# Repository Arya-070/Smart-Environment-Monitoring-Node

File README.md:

# 🌿 Smart Environment Monitoring Node  
📡 ESP32-WROOM-32 + LoRa + BME280 + OLED | USB Powered | Custom PCB

──────────────────────────────────────────────

## 📌 Overview

This project is a compact, power-efficient, and long-range **environment monitoring system** based on the **ESP32-WROOM-32 chip**. It measures temperature, humidity, and pressure using the **BME280 sensor**, displays real-time values on a **0.96” OLED display**, and transmits the data via **LoRa SX1262** for remote monitoring.  

All hardware is designed on a **custom 2-layer PCB** and powered via a **USB Micro-B port**, with built-in USB-to-Serial conversion and auto-upload support for seamless firmware flashing.

---

## ✨ Project Highlights

• 🔧 Fully custom-designed PCB (2-layer) using KiCad  
• 📡 Long-range LoRa communication using SX1262  
• 🌡 Environmental monitoring using BME280  
• 🖥 Local data display via 0.96” I2C OLED  
• 🔌 USB-powered with CH340C USB-to-Serial interface  
• ⏩ Auto-upload circuit using NPN transistors  
• 🔁 Reset + Boot buttons like ESP32 Dev board  
• 📍Test points for VCC & GND for easy debugging  
• 🔋 AMS1117-based 3.3V regulator (if needed)  

---

## 📌  ESP32 GPIO Pinout & Connections 

| GPIO Pin   | Connected To              | Function / Role                     |
|------------|---------------------------|--------------------------------------|
| GPIO 0     | Q2 (Transistor)           | BOOT (Auto Upload via DTR)          |
| GPIO 1 (TXD)| CH340C RXD               | UART Transmission                    |
| GPIO 3 (RXD)| CH340C TXD               | UART Reception                       |
| GPIO 4     | SX1262 NSS                | SPI Chip Select (LoRa)              |
| GPIO 5     | SX1262 BUSY               | LoRa Busy Status                    |
| GPIO 14    | SX1262 SCK                | SPI Clock                           |
| GPIO 18    | SX1262 MISO               | SPI MISO                            |
| GPIO 19    | SX1262 MOSI               | SPI MOSI                            |
| GPIO 21    | OLED SDA                  | I2C Data (Display)                  |
| GPIO 22    | OLED SCL                  | I2C Clock (Display)                 |
| GPIO EN    | Q1 (Transistor)           | EN (Auto Reset via RTS)             |
| GPIO 23    | SX1262 DIO1               | LoRa Interrupt                      |
| GPIO 16    | SX1262 DIO2               | LoRa General-Purpose I/O            |
| GPIO 17    | BME280 SCK                | SPI Clock (Sensor)                  |
| GPIO 2     | LED (Optional)            | Debug LED Output                    |
| GPIO 13    | SX1262 NSS (2nd)          | SPI Slave Select (Alt, Unused?)     |
| GPIO 12,15 | —                         | Reserved / Available for future use |

🔍 *See schematic for exact net labels and detailed mapping.*

---

## 🔍 Use Case Acknowledgement

This project is ideal for:

• Agricultural field condition monitoring  
• Weather stations (indoor or outdoor)  
• Smart home environmental logging  
• Educational IoT demonstrations  
• Smart city sensor node deployment  
• Remote sensing with LoRa infrastructure

---

## 🧭 System Architecture

---

## 🧩 Component Summary

| No. | Component              | Interface | Description                                  |
|-----|------------------------|-----------|----------------------------------------------|
| 1   | ESP32-WROOM-32         | -         | Main MCU (WiFi, BLE, Dual Core)              |
| 2   | BME280 (SPI)           | SPI       | Temp, Pressure, Humidity sensor              |
| 3   | OLED 0.96” Display     | I2C       | SSD1306, 128x64 pixel display                |
| 4   | SX1262IMLTRT (QFN)     | SPI       | LoRa transceiver (433/868/915MHz)            |
| 5   | AMS1117-3.3V Regulator | Power     | Converts 5V USB to 3.3V (optional)           |
| 6   | CH340C USB to Serial   | UART      | USB programming interface                    |
| 7   | 40MHz Crystal Oscillator| CLK      | ESP32 clock source                           |
| 8   | Push Buttons (2x)      | GPIO/EN   | Boot and Reset functionality                 |
| 9   | LED + Resistor         | Power     | Power-on indicator                           |
| 10  | Capacitors (0.1µF, 10µF)| Power    | Decoupling & filtering                       |
| 11  | Test Points (TP1/TP2)  | -         | For debugging (3.3V and GND)                 |
| 12  | Micro USB Port         | Power     | Power + Serial communication                 |
| 13  | Resistors (10k, 1k)    | Logic     | Pull-ups and transistor base resistors       |
| 14  | NPN Transistors (x2)   | Auto Upload | Connected to DTR/RTS                        |
| 15  | Conn_01x2 / 01x4 / 01x8| Header    | GPIO/I2C/Power breakout (optional)           |

---

## 💾 Firmware Summary

• Platform: Arduino Framework  
• Libraries:
  - `Adafruit_BME280` (SPI)
  - `U8g2lib` / `Adafruit_SSD1306`
  - `RadioLib` or `LoRa` for SX1262
• Logic:
  - Read sensor values → Display on OLED → Send via LoRa
• Auto-upload handled via CH340C + transistor toggling of IO0 and EN

---

## 🧪 Test Points

| Label | Connected To | Use                      |
|-------|--------------|---------------------------|
| TP1   | 3.3V         | Voltage test/debug        |
| TP2   | GND          | Ground continuity check   |

---

## 📦 Folder Structure

```
Smart-Environment-Monitoring-Node/
│
├── SCHEMATIC/
│   ├── Smart_Env_monitoring_Node.kicad_sch
│   ├── Smart_Env_monitoring_Node.pdf
│  
├── Backup_ZIP
│
├── PCB/
│   ├──  Smart_Env_monitoring_Node.kicad_pcb
│   ├──  Smart_Env_monitoring_Node.kicad_pro
│   ├──  Smart_Env_monitoring_Node.csv
│   ├── Gerber_Files/
│   ├── F_Cu.gbr
│   ├── B_Cu.gbr
│   ├── Edge_Cuts.gbr
│   ├── Drill.drl
│   └── ...etc
│
├── Firmware/
│   └── main.ino 
│
├── Libraries/
│   ├── COMPONENTS_DOWNLOADED/
│   └── MY_LIBRARY_MODIFIED.pretty/
│
├── Images/
│   ├── 3D_View.png
│   ├── Top_Layout.png
│   ├── Bottom_Layout.png
│   └── System_Architecture.png
│
├── README.md
└── .gitignore
```

---

## 📐 PCB Design Summary

• Software: KiCad 7.0  
• Layers: 2 (Top & Bottom)  
• Antenna zone: Keep-out area maintained  
• Crystal zone: No trace below (as per layout best practices)  
• Ground pour: Yes, with via stitching  
• Auto-upload near CH340C  
• I2C lines shared between OLED and future I2C sensors

---

## 📌 Optional Headers

| Header     | Size | Description                    |
|------------|------|--------------------------------|
| Conn_01x2  | 2-pin | External battery connection    |
| Conn_01x4  | 4-pin | I2C expansion header           |
| Conn_01x8  | 8-pin | GPIO access (debug/expansion) |

---

## 🔮 Future Improvements

• Add onboard Li-ion battery charging (TP4056)  
• Use low-dropout regulator instead of AMS1117  
• Enable I2C/SPI switch for BME280  
• Add buzzer or notification LED  
• Add deep sleep mode for power efficiency  
• Add mobile enclosure + mounting holes

---

## 📜 License

Licensed under the MIT License.  
Feel free to use, modify, and share — just give credit. 

---

## 🤝 Acknowledgements

This project is inspired by real-world smart sensing requirements and open hardware communities. Thanks to Espressif Systems, Adafruit, and the KiCad team for empowering makers with tools and documentation.

---

## 📬 Contact / Contribution

• Found something useful? Leave a ⭐ on GitHub.  
• Found a bug or want to improve? Fork and PRs are welcome.  
• Reach out for collaboration or questions!

Let’s make sensing smarter, together. 🌍

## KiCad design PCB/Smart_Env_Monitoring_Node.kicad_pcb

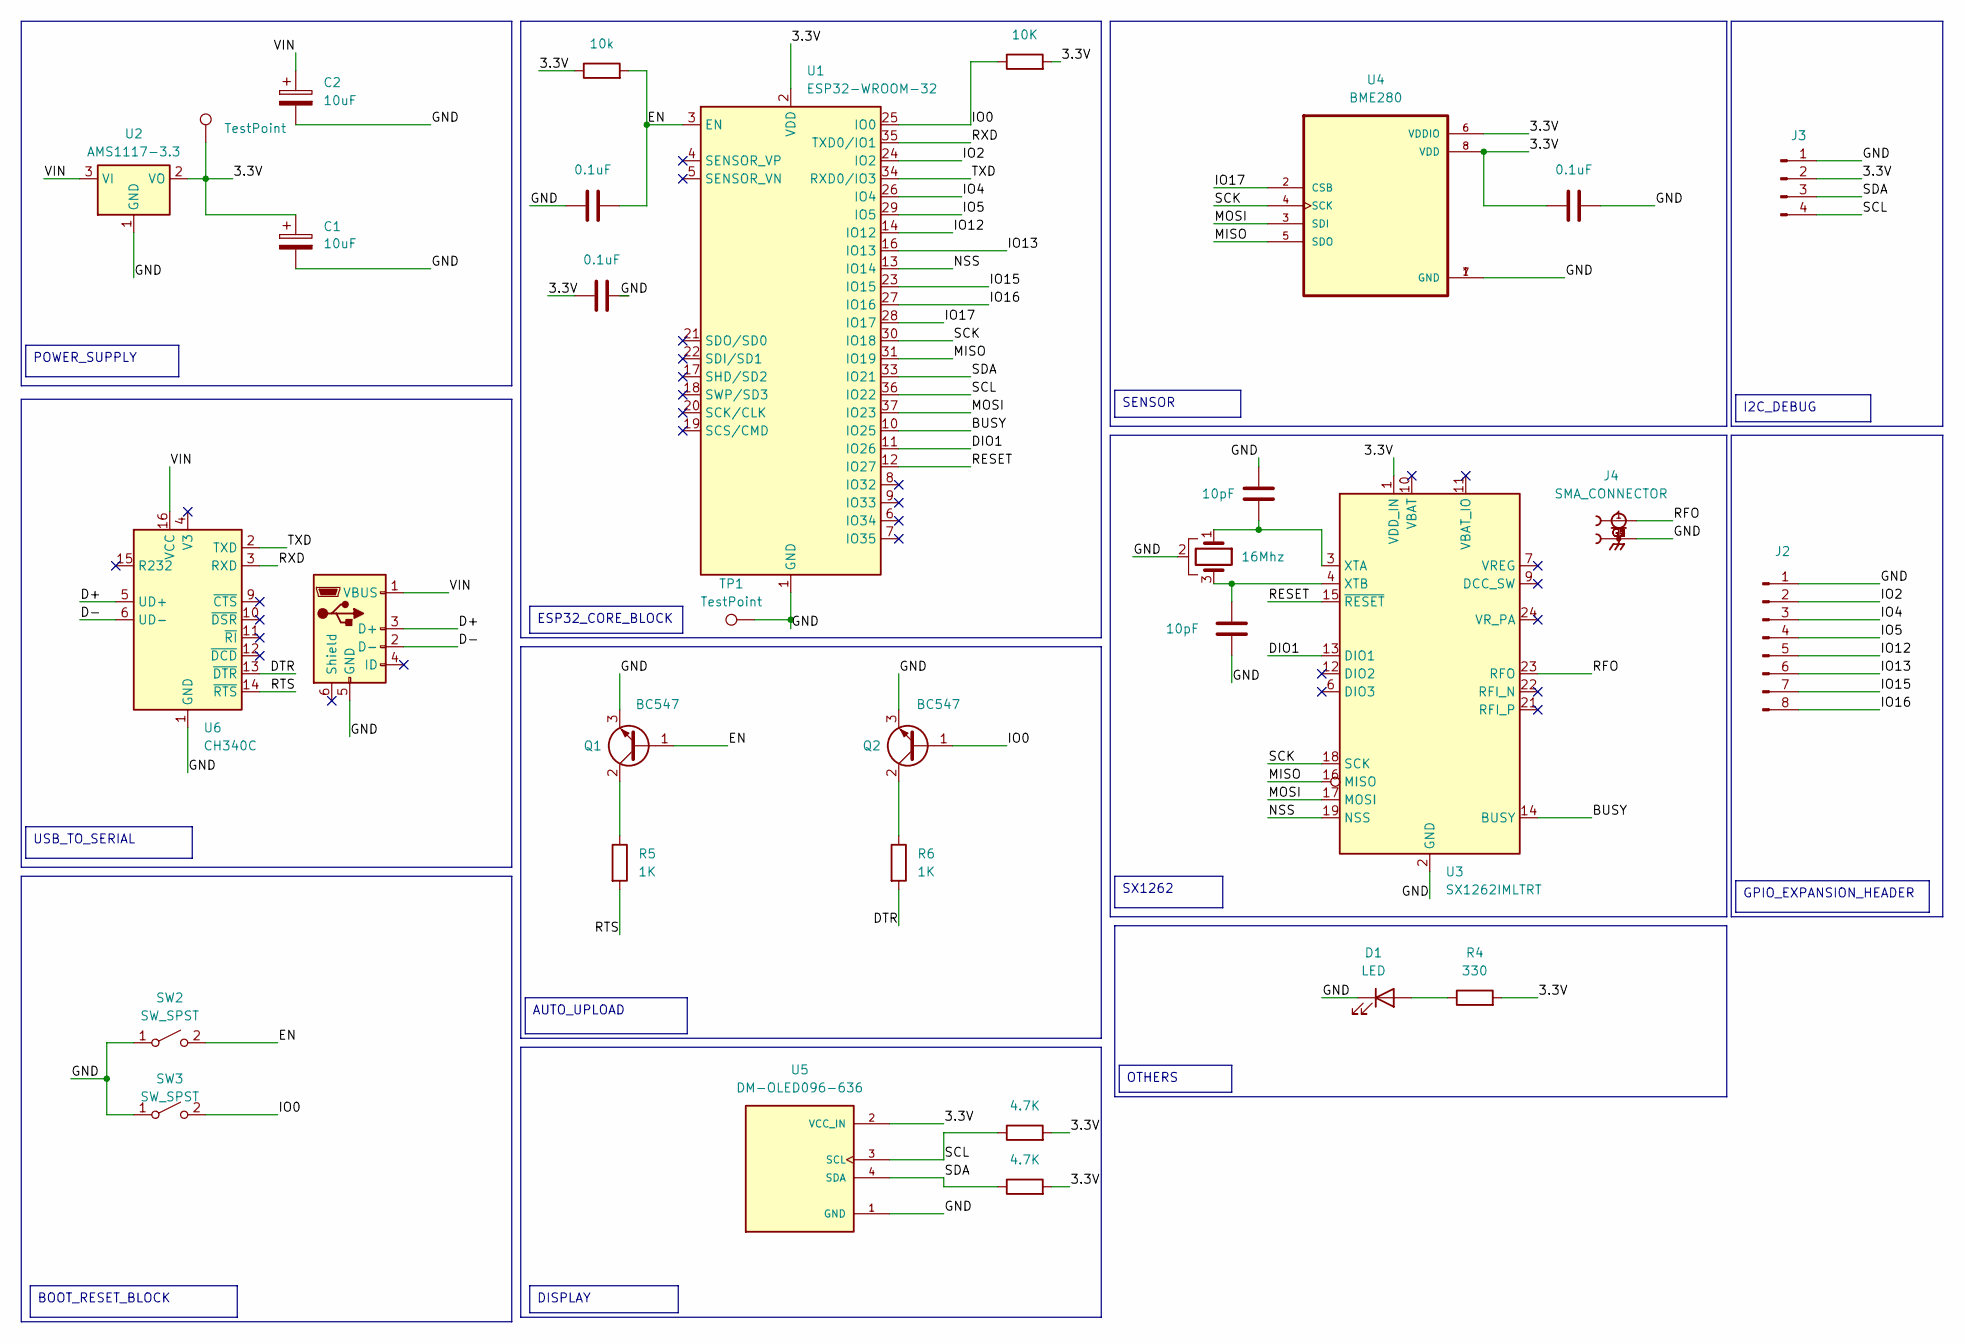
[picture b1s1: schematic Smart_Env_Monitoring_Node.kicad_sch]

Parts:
C1, C2: 10uF; CP_Radial_D5.0mm_P2.00mm
C3, C4, C5: 0.1uF; C_0603_1608Metric_Pad1.08x0.95mm_HandSolder
C6, C7: 10pF; C_0603_1608Metric_Pad1.08x0.95mm_HandSolder
D1: LED; LED_D5.0mm_modified
J1: USB_B_Micro; USB_Micro-B_Molex_47346-0001
J2: Conn_01x08_Pin; PinSocket_1x08_P2.54mm_Vertical
J3: Conn_01x04_Pin; PinSocket_1x04_P2.54mm_Vertical
J4: SMA_CONNECTOR; LPRS_SMA_CONNECTOR; PARTREV 1.3
Q1, Q2: BC547; SOT-23
R1: 10K; R_0805_2012Metric_Pad1.20x1.40mm_HandSolder
R2: 10k; R_0805_2012Metric_Pad1.20x1.40mm_HandSolder
R3, R7: 4.7K; R_0805_2012Metric_Pad1.20x1.40mm_HandSolder
R4: 330; R_0805_2012Metric_Pad1.20x1.40mm_HandSolder
R5, R6: 1K; R_0805_2012Metric_Pad1.20x1.40mm_HandSolder
SW2, SW3: SW_SPST; SW_SPST_TL3342
TP1, TP2: TestPoint; TestPoint_Pad_D1.0mm
U1: ESP32-WROOM-32; ESP32-WROOM-32_MODIFIED
U2: AMS1117-3.3; SOT-223-3_TabPin2
U3: SX1262IMLTRT; QFN-24-1EP_4x4mm_P0.5mm_EP2.6x2.6mm
U4: BME280; PSON65P250X250X100-8N
U5: DM-OLED096-636; MODULE_DM-OLED096-636; PARTREV 2018-09-10
U6: CH340C; SOIC-16_3.9x9.9mm_P1.27mm
Y1: 16Mhz; Crystal_SMD_3225-4Pin_3.2x2.5mm

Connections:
/3.3V: C1.1, C4.1, C5.1, J3.2, R1.2, R2.1, R3.2, R4.2, R7.2, TP2.1, U1.2 (VDD), U2.2 (VO), U3.1 (VDD_IN), U4.6 (VDDIO), U4.8 (VDD), U5.2 (VCC_IN)
/BUSY: U1.10 (IO25), U3.14 (BUSY)
/D+: J1.3 (D+), U6.5 (UD+)
/D-: J1.2 (D-), U6.6 (UD-)
/DIO1: U1.11 (IO26), U3.13 (DIO1)
/DTR: R6.2, U6.13 (~DTR)
/EN: C3.2, Q1.1 (B), R2.2, SW2.2 (B), U1.3 (EN)
/GND: C1.2, C2.2, C3.1, C4.2, C5.2, C6.1, C7.2, D1.1 (K), J1.5 (GND), J2.1, J3.1, J4.G1, J4.G2, J4.G3, J4.G4, Q1.3 (E), Q2.3 (E), SW2.1 (A), SW3.1 (A), TP1.1, U1.1 (GND), U1.15 (GND), U1.38 (GND), U1.39 (GND), U2.1 (GND), U3.2 (GND), U3.5 (GND), U3.8 (GND), U3.20 (GND), U3.25 (GND), U4.1 (GND), U4.7 (GND), U5.1 (GND), U6.1 (GND), Y1.2
/IO0: Q2.1 (B), R1.1, SW3.2 (B), U1.25 (IO0)
/IO2: J2.2, U1.24 (IO2)
/IO4: J2.3, U1.26 (IO4)
/IO5: J2.4, U1.29 (IO5)
/IO12: J2.5, U1.14 (IO12)
/IO13: J2.6, U1.16 (IO13)
/IO15: J2.7, U1.23 (IO15)
/IO16: J2.8, U1.27 (IO16)
/IO17: U1.28 (IO17), U4.2 (CSB)
/MISO: U1.31 (IO19), U3.16 (MISO), U4.5 (SDO)
/MOSI: U1.37 (IO23), U3.17 (MOSI), U4.3 (SDI)
/NSS: U1.13 (IO14), U3.19 (NSS)
/RESET: U1.12 (IO27), U3.15 (~RESET)
/RFO: J4.1, U3.23 (RFO)
/RTS: R5.2, U6.14 (~RTS)
/RXD: U1.35 (TXD0/IO1), U6.3 (RXD)
/SCK: U1.30 (IO18), U3.18 (SCK), U4.4 (SCK)
/SCL: J3.4, R3.1, U1.36 (IO22), U5.3 (SCL)
/SDA: J3.3, R7.1, U1.33 (IO21), U5.4 (SDA)
/TXD: U1.34 (RXD0/IO3), U6.2 (TXD)
/VIN: C2.1, J1.1 (VBUS), U2.3 (VI), U6.16 (VCC)
unnamed: D1.2 (A), R4.1
unnamed: Q1.2 (C), R5.1
unnamed: Q2.2 (C), R6.1
unnamed: C6.2, U3.3 (XTA), Y1.1
unnamed: C7.1, U3.4 (XTB), Y1.3

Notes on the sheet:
GPIO_EXPANSION_HEADER
OTHERS
BOOT_RESET_BLOCK
SX1262
USB_TO_SERIAL
SENSOR
ESP32_CORE_BLOCK
DISPLAY
I2C_DEBUG
POWER_SUPPLY
AUTO_UPLOAD

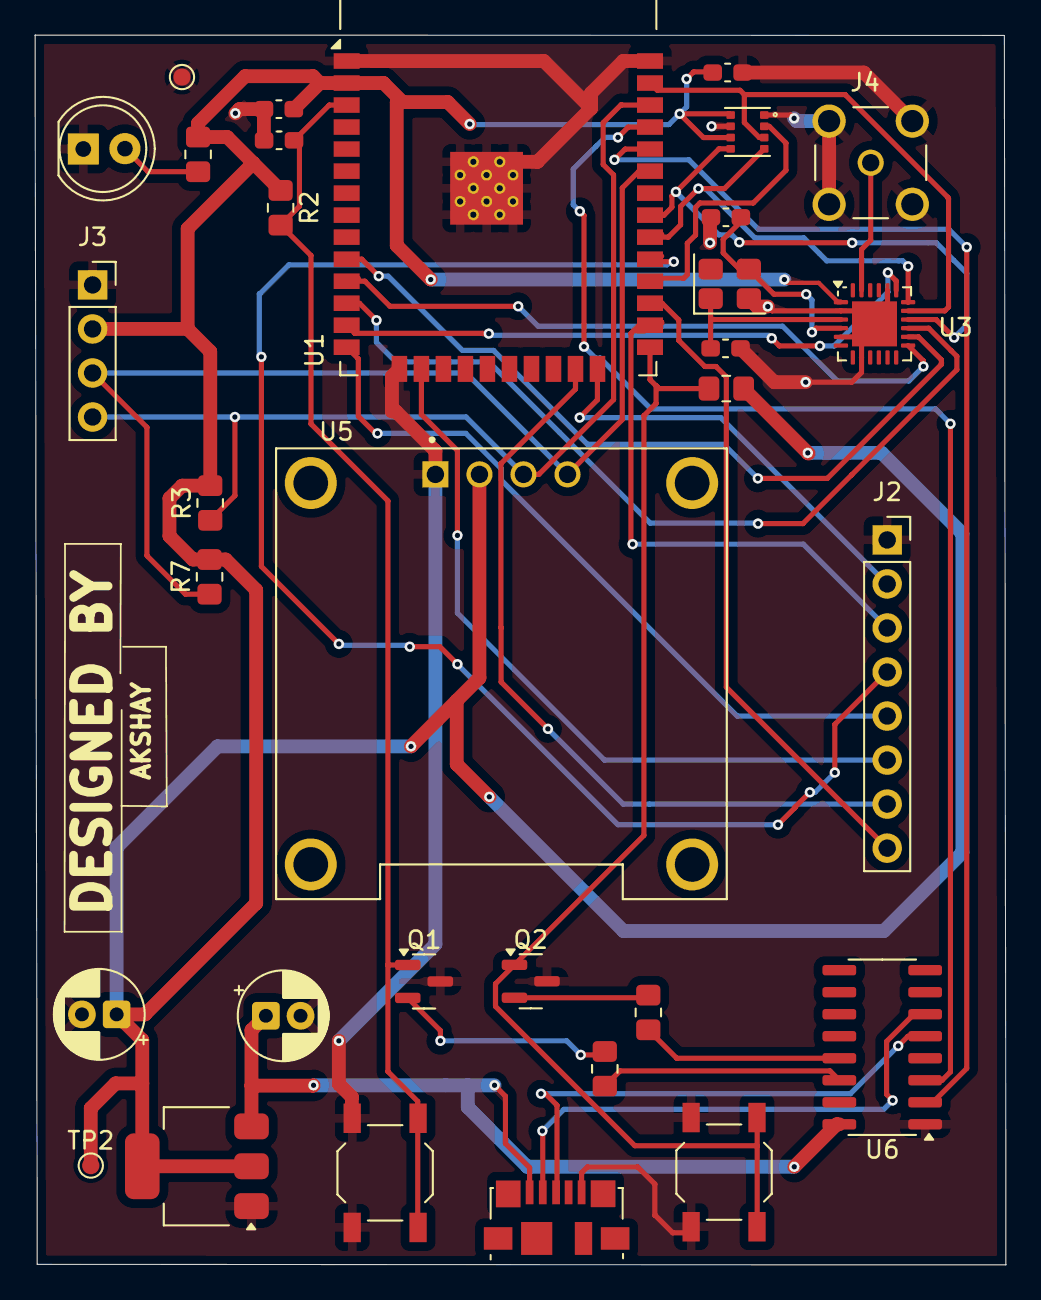
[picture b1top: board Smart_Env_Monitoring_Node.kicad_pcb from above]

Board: 2 copper layers, 56.0 x 70.9 mm, 32 parts (0 on the bottom side), 34 nets.

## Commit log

2025-07-14 Initial commit: Added full Smart Environment Monitoring Node project
2025-07-14 Rename Smart_Env_Monitoring_Node.pdf.pdf to Smart_Env_Monitoring_Node.pdf
2025-07-14 Rename Smart_Env_Monitoring_Node.kicad_pro.kicad_pro to Smart_Env_Monitoring_Node.kicad_pro
2025-07-14 Create FIRMWARE
2025-07-14 Rename 3D_View.png.png to 3D_View.png
2025-07-14 Rename Bottom_Layout.png.png to Bottom_Layout.png
2025-07-14 Rename Top_Layout.png.png to Top_Layout.png
